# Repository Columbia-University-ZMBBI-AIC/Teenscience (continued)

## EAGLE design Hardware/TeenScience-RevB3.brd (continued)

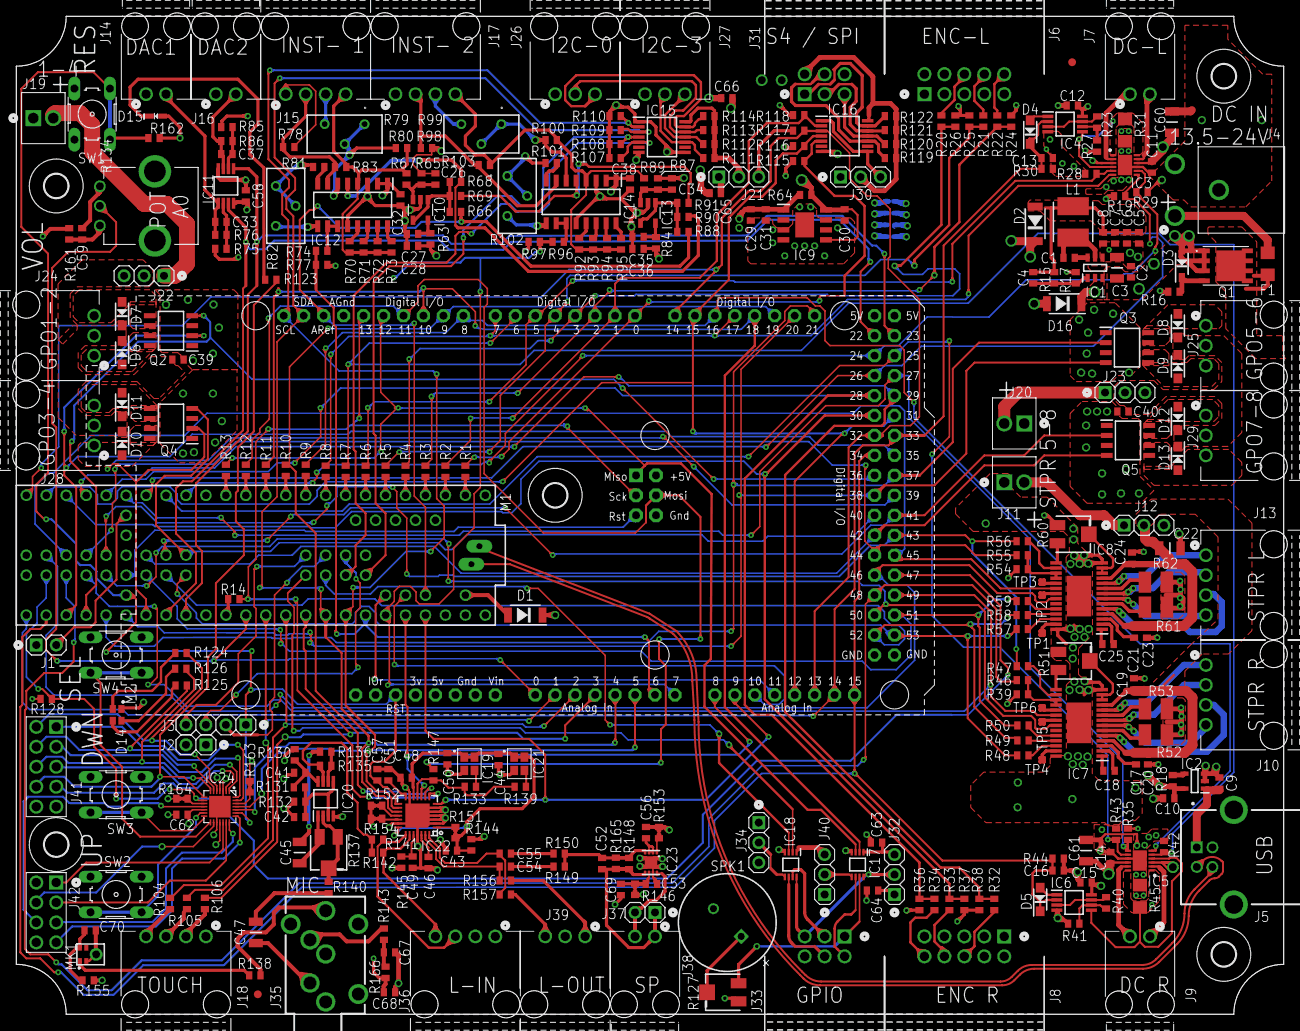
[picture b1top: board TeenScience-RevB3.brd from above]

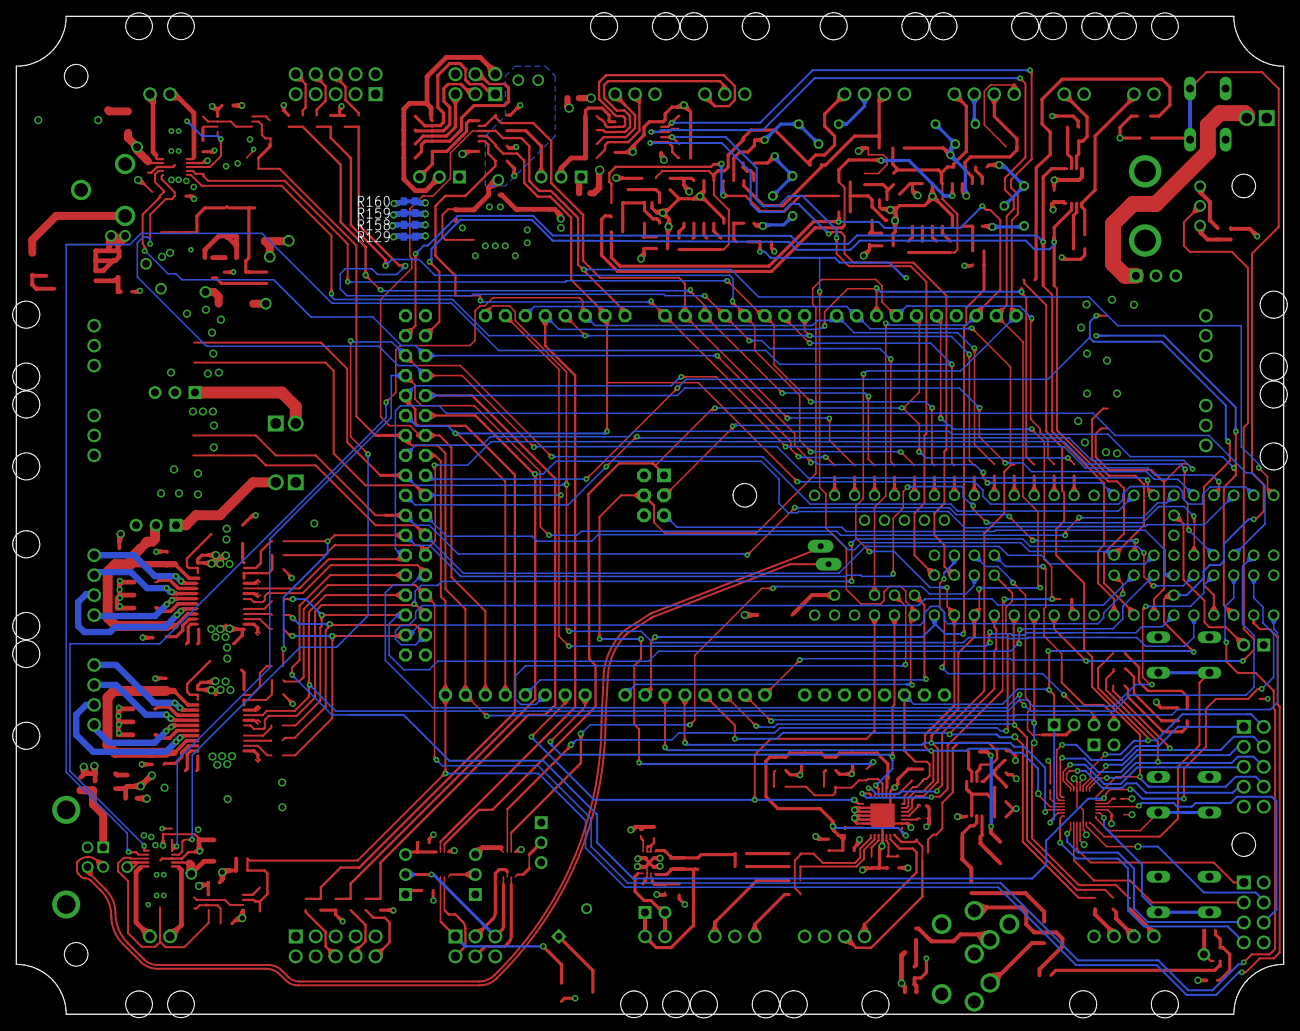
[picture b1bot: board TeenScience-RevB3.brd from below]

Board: 4 copper layers, 161.3 x 127.0 mm, 349 parts (4 on the bottom side), 290 nets.

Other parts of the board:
U$1, U$2, U$4, U$5, U$7: 3,0

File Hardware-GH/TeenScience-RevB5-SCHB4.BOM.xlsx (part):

| Columbia University TeenScience Platform ZIAIC00025 REVB4- May 2020 | Rev by R. Hormigo
Qty | DESCRIPTION | Value | Package | Parts | MNF | MPN | VENDOR | Column1
31 | Multilayer Ceramic Capacitor (MLCC)X7R 0603, 0.10uF 5%, 50V | 0.10uF | MLCC_0603 | C1, C2, C11, C12, C14, C15, C17, C19, C20, C21, C23, C24, C28, C30, C31, C32, C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 | AVX | 06035C104JAT2A | Mouser
2 | Multilayer Ceramic Capacitor (MLCC)X7R 0603, 0.010uF 5%, 50V | 0.010uF | MLCC_0603 | C18, C25, C57 | AVX | 06035C103JAT2A | Mouser
6 | Ceramic Capacitor X7R 1206 35V 10uF | 10uF | MLCC_1206 | C3, C22, C45, C47, C60, C61 | TAIYO YUDEN | GMK316AB7106KL-TR
4 | Multilayer Ceramic Capacitor (MLCC)C0G HF 0603, 47pF 1%, 100V | 47pF | MLCC_0603 | C4, C33, C37, C52 | Murata | GCM1885C2A470FA16D | Mouser
15 | Multilayer Ceramic Capacitor (MLCC)X5R 0603, 10uF 10%, 10V | 10uF | MLCC_0603 | C5, C6, C7, C8, C10, C41, C49, C50, C51, C54, C55, C56, C67, C68, C69 | AVX | 0603ZD106KAT2A | Mouser
12 | Multilayer Ceramic Capacitor (MLCC)X7R 0603, 1uF 10%, 35V | 1uF | MLCC_0603 | C9, C13, C16, C26, C27, C29, C34, C35, C42, C46, C59, C70 | TDK | CGA3E1X7R1V105K080AC | Mouser
3 | Nexperia PMEG3030EP,115 SMT Schottky Diode, 30V 3A, 2-Pin SOD128 | PMEG3030 | SOD_128_DIODE | D1, D2, D16 | Nexperia | PMEG3030EP,115
1 | LED DIODE RGB, 5mA, SMT 2X2X0.9mm | RGB | SON95P2X2X1-RGB_LED | D14 | Cree | CLMVC-FKA-CLBDGL7LBB79353 | Mouser
1 | LED DIODE Green, 2mA, 1.9V, SMT 0603 | Green | LED_0603 | D15 | Kingbright | APTD1608LCGCK | Mouser
1 | ZENNER DIODE, 0.5W, 9.1V, SMT SOD123-2 | 9.1V | SOD3716X135N_DIODE | D3 | ON Semi | MMSZ9V1T1G | Mouser
2 | Low forward voltaage Schottky diode | PMEG2010 | SOD-123FL | D4, D5 | Nexperia | PMEG2010ER,115
8 | Rectifier Diode 2A 200V. SOD−123FL | NHP220 | SOD-123FL | D6, D7, D8, D9, D10, D11, D12, D13 | ON Semi | NHP220SFT3G | Mouser
1 | 3A Fast Fuse 1206-3.2X1.6MM | F3A | 1206-3.2X1.6MM | F1 | Schurter | 3413.0121.24
1 | Switching Voltage Regulators DCDC Conv HV Buck TSOT26 | AP63200 | SOT95P280X100-6N | IC1 | Diodes Inc. | AP63200WU-7 | Mouser
2 | 10MHz, IO Rail-to-Rail Op Amp, 12V 2mA max, high current out, SOT-23 | LT1797 | SOT23-5 | IC10, IC13 | LinearTechnologies | LT1797CS5#TRMPBF | Mouser
2 | INA125U, Instrumention Amplifier, 0.25mV Offset, 78dB CMRR, 5V, 16-Pin SOIC | INA125 | SOIC16-127P600X175 | IC12, IC14 | Texas Instruments | INA125U
2 | 4-Bit Bidirectional Multi-Voltage Level Translator for Open-Drain & Push- Pull | LSF0204 | TSSOP14 | IC15, IC16 | Texas Instruments | LSF0204PWR
2 | Texas Instruments SN74LVC2T45DCUR, Voltage Level Translator, Bus Transceiver, 3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 | 74LVC2T45 | VSSOP8-DCU-050P | IC17, IC18 | Texas Instruments | SN74LVC2T45DCUR
1 | IC Oscillator 1.6 to 3.6V 50PPM 24.576MHz. 2.5 X 2mm | 24.576MHz | 2.5X2-4-PAD | IC19 | Epson | SG-210STF 24.5760ML3 | Mouser
1 | LTC4411CS8 battery/mains PS controller LTC4411ES5#TRMPBF, Battery Charge Contro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 | LTC4411 | SOT95P280X100-5N | IC2 | Linear Technology | LTC4411ES5#TRMPBF
1 | IC Oscillator 1.6 to 3.6V 50PPM 11.2896MHz. 2.5 X 2mm | 11.2896MHz | 2.5X2-4-PAD | IC21 | Epson | SG-210STF 11.2896ML3 | Mouser
1 | Audio Codec 108dB 216KHz 32bit 3.3V with PLL. QFN28 | AK4558EN | QFN-28-5MM-0.5P-PAD | IC22 | AKM | AK4558EN | Digikey
1 | Audio Amplifier ClassAB 1.5W 8Ohm with 4MHz GBP. LFCSP-8 | SSM2211 | LFCSP8_3X3 | IC23 | Analog Devices | SSM2211CPZ-REEL7 | Mouser
1 | Interface - I/O Expanders 16 CHAN LOW VOLT I2C GPIO +PWM | SX1509 | QFN-28-4MM-0.4P-PAD | IC24 | SEMTECH | SX1509BIULTRT
2 | DC Motor H Bridge Driver 4.5 to 36V, 2.5A max SMT TDFN-EP 12 3X3mm | MAX14870 | TDFN12-EP | IC3, IC5 | Maxim | MAX14870ETC+T | Mouser
4 | 36-V, Single-Supply, 10-MHz, Rail-to-Rail Output, Dual Operational Amplifier | TLV2172 | VSSOP8-DGK-065P | IC4, IC6, IC11, IC20 | Texas Instruments | TLV2172IDGKR
2 | 2.5A Bipolar Stepper Motor Driver with On-Chip 1/32 Microstepping Indexer (Step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 | DRV8825PWPR | TSSOP28-PWR | IC7, IC8 | Texas Instruments | DRV8825PWPR
1 | ROHM BDJ2FC0WEFJ-E2 LDO HTSOP 8 | BDJ2FC0 | SOIC8-PAD127P600X100 | IC9 | ROHM Semi | BDJ2FC0WEFJ-E2
3 | Header Straight Male 1 X 2 (2.54mm square) 6.75mm post | HDR 1x2 ST-M | HDR_1X2 | J1, J2, J37 | Amphenol FCI | 77311-124-02LF | Mouser
6 | Header RA Male 1X4 Gold Shrouded 0.1" | HDR 1X4 RA-M | HDR_1X4RAS | J10, J13, J15, J17, J18, J36 | Molex | 70555-0073 | Mouser
3 | Phenix Screw terminal 0.1" X 2 | Phoenix 1X2 | TE_282834-2_PHOENIX2 | J11, J19, J20 | TE | 282834-2 | Mouser
8 | Header Straight Male 1 X 3 (2.54mm square) 6.75mm post | HDR 1x3 ST-M | HDR_1X3 | J12, J21, J22, J23, J30, J32, J34, J40 | Amphenol FCI | 77311-124-03LF | Mouser
7 | Header RA Male 1X3 Gold Shrouded 0.1" | HDR 1X3 RA-M | HDR_1X3RAS | J24, J25, J26, J27, J28, J29, J39 | Molex | 70555-0072 | Mouser
1 | Header Straight Male 1 X 4 (2.54mm square) 6.75mm post | HDR 1x4 ST-M | HDR_1X04 | J3 | Amphenol FCI | 77311-124-04LF | Mouser
2 | Header RA Male 2X3 Gold Shrouded 0.1" | HDR 2X3 RA-M | HDR_2X3M_RAS | J31, J33 | 3M | 30306-5002HB | Mouser
1 | Phone Connectors 3.5mm Audio Jack Stereo with Switch | JACK 3.5mm | AUDIO-JACK-SJ1-3533NS | J35 | CUI | SJ1-3535NS
1 | DC Power Jack, Panel Mount, 2.1mm, Standard Bushing, Right Angle PC | 2.1 ID | DCJACK-721RA | J4 | Switchcraft | 721RA
1 | Header Right Angle 2 X 5 (2.54mm square) 5.84 mm mating | HDR 2x5 RA-M | HDR_2X5M_RAHDR | J41 | SAMTEC | TSW-104-10-G-D-RA | Mouser
1 | Header Right Angle 2 X 4 (2.54mm square) 5.84 mm mating | HDR 2x4 RA-M | HDR_2X4M_RAHDR | J42 | SAMTEC | TSW-104-08-G-D-RA | Mouser
1 | USB B STANDARD RA, TH | USB-B-RA | USB-B | J5 | MOLEX | 67068-8000 | Mouser
2 | Header RA Male 2X5 Gold Shrouded 0.1" | HDR 2X5 RA-M | HDR_2X5M_RAS | J6, J8 | 3M | 30310-5002HB | Mouser
5 | Header RA Male 1X2 Gold Shrouded 0.1" | HDR 1X2 RA-M | HDR_1X2RAS | J7, J9, J14, J16, J38 | Molex | 70555-0071 | Mouser
1 | TDK VLS-EX Series Type 5045 Shielded Wire-wound SMD Inductor with a Ferrite Cor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 | 10uH | IND_5X5MM-5045 | L1 | TDK | VLS5045EX-100M
1 | Teensy 3.6, 3.3V, 180MHz controller with no pins | Teensy 3.6 | TEENSY_3.6 | M1 | PJRC | TEENSY36 (No pins) | Sparkfun
1 | Teensy 3.5/3.6 Socket Kit | Connector Kit | See datasheet directions | M1 (Pins) | Tall Dog Electronics | Teensy 3.5/3.6 Socket Kit | Tindie.com | https://d3s5r33r268y59.cloudfront.net/datasheets/8746/2017-0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
1 | Wideband 80KHz MEMS 2.65X3.5mm MIC 400Ohm 145uA 1.5-3.6V | MIC | SPH6611_MEMS_2.65X3.50 | MK1 | KnowLess | SPH6611LR5H-1 | Mouser
1 | P CH MOSFET 40V, 100A, 1.4mOhm, SMT DFN 8 5.1x6.3 | FDWS9509L | FDN8_5.1X6.3 | Q1 | ON Semi | FDWS9509L-F085 | Mouser
4 | Diodes Inc DMG4822SSDQ-13 Dual N-channel MOSFET Transistor, 10 A, 30 V, 8-Pin S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 | DMG4822 | SOIC8-127P60 | Q2, Q3, Q4, Q5 | Diodes Inc. | DMG4822SSDQ-13
19 | Thick Film Resistor 0603, 20 Ω ,1%, 0.1W | 20 Ω | R0603 | R1, R2, R3, R4, R5, R6, R7, R8, R9, R10, R11, R12, R13, R14, R63, R84, R144, R1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 | Vishay | CRCW060320R0FKEA | Mouser
7 | Thick Film Resistor 0603, 1.0 kΩ ,1%, 0.1W | 1.0 kΩ | R0603 | R104, R105, R106, R111, R112, R113, R114 | Vishay | CRCW06031K00FKEA | Mouser
2 | Thick Film Resistor 0603, 360 Ω ,1%, 0.1W | 360 Ω | R0603 | R123, R124 | Vishay | CRCW0603360RFKEA | Mouser
5 | Thick Film Resistor 0603, 100 Ω ,1%, 0.1W | 100 Ω | R0603 | R125, R126, R138, R156, R157 | Vishay | CRCW0603100RFKEA | Mouser
1 | SM Single turn Top Screw Trimmer 1K | 1K | SM-4.5X4.5-TRIM | R127 | BOURNS | 3314J-2-102E
11 | 0603 Resistor Shunt (no part placed) | SHUNT | R0603-SHORT | R129, R146, R151, R152, R153, R154, R158, R159, R160, R163, R164
1 | Audio single pot. 10K Vertical 20mm,1B Alps Potentiometer RK09D Series with a 6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 | 10K | RK09-ALPS-VERT-POT | R134 | ALPS | RK09D1130C1B
1 | SM Single turn Top Screw Trimmer 200K | 200K | SM-4.5X4.5-TRIM | R137 | BOURNS | 3314J-2-204E
1 | Thick Film Resistor 0603, 56 kΩ ,1%, 0.1W | 56 kΩ | R0603 | R15 | Vishay | CRCW060356K0FKEA | Mouser
1 | Thick Film Resistor 0603, 100 kΩ ,1%, 0.1W | 100 kΩ | R0603 | R16 | Vishay | CRCW0603100KFKEA | Mouser
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
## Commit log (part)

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2023-01-09 Upload to new rep
